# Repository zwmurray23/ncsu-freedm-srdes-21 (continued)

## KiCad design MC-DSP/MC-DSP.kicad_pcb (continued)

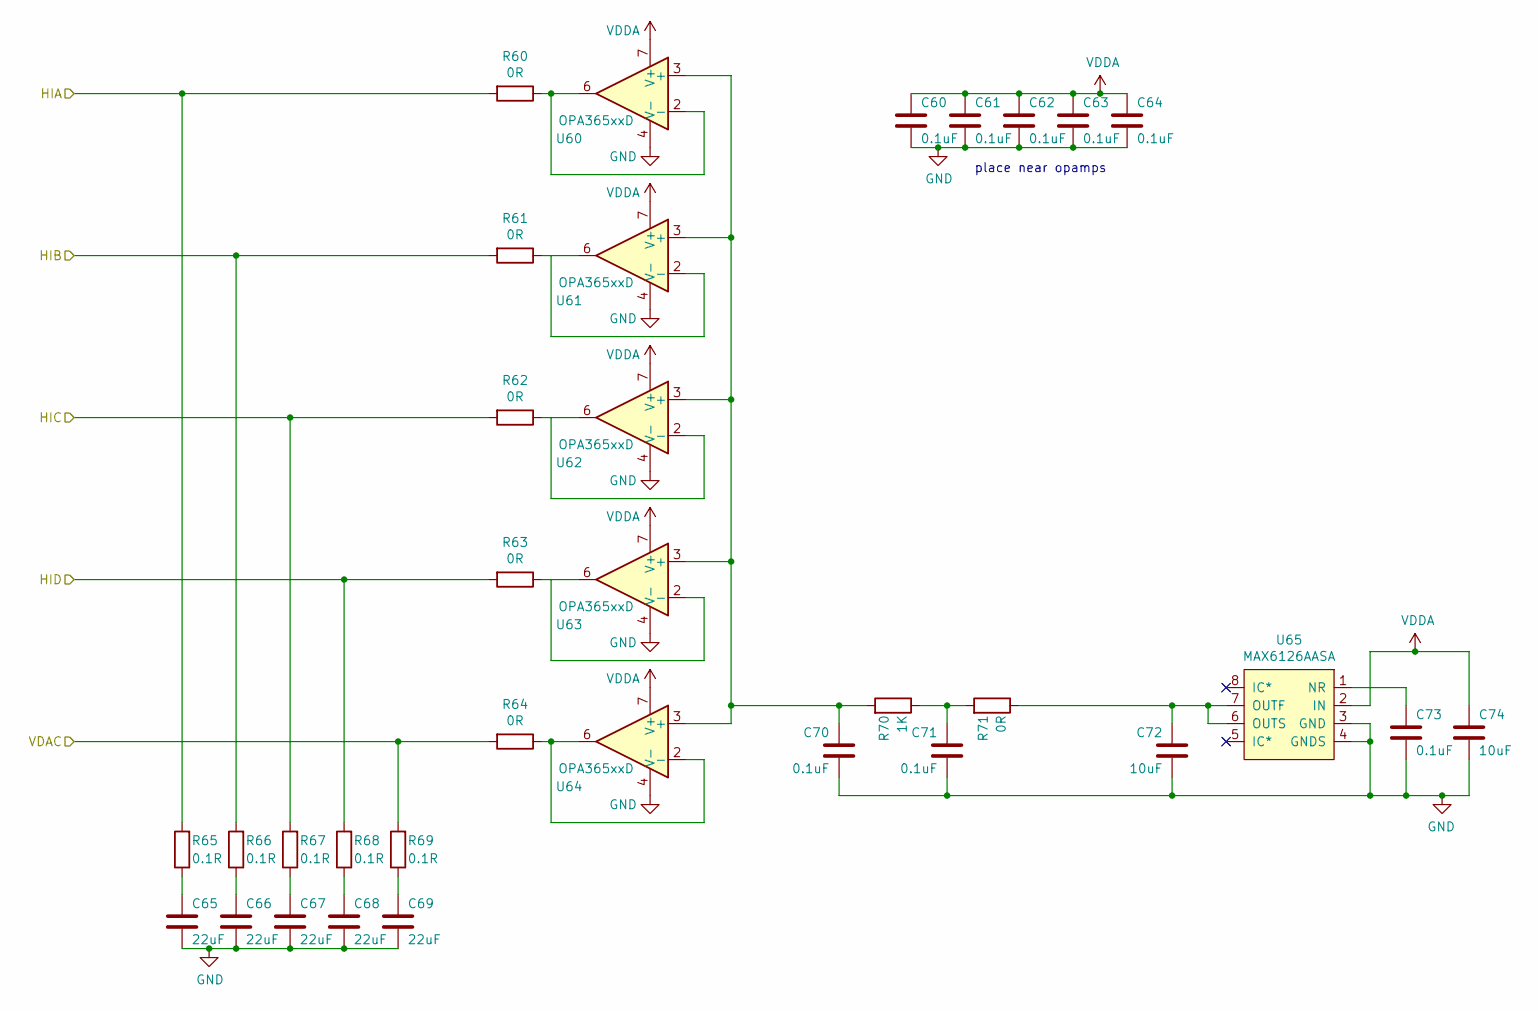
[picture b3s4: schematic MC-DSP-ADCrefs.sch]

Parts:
C60, C61, C62, C63, C64, C70, C71, C73: 0.1uF; C_0603_1608Metric_Pad1.08x0.95mm_HandSolder
C65, C66, C67, C68, C69: 22uF; C_0603_1608Metric_Pad1.08x0.95mm_HandSolder
C72, C74: 10uF; C_0603_1608Metric_Pad1.08x0.95mm_HandSolder
R60, R61, R62, R63, R64, R71: 0R; R_0603_1608Metric_Pad0.98x0.95mm_HandSolder
R65, R66, R67, R68, R69: 0.1R; R_0603_1608Metric_Pad0.98x0.95mm_HandSolder
R70: 1K; R_0603_1608Metric_Pad0.98x0.95mm_HandSolder
U60, U61, U62, U63, U64: OPA365xxD; SOIC-8_3.9x4.9mm_P1.27mm
U65: MAX6126AASA; SOIC-8_3.9x4.9mm_P1.27mm

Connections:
/ADCrefs/HIA: R60.2, R65.2; also elsewhere on the board
/ADCrefs/HIB: R61.2, R66.2; also elsewhere on the board
/ADCrefs/HIC: R62.2, R67.2; also elsewhere on the board
/ADCrefs/HID: R63.2, R68.2; also elsewhere on the board
GND: C60.1, C61.1, C62.1, C63.1, C64.1, C65.1, C66.1, C67.1, C68.1, C69.1, C70.1, C71.1, C72.1, C73.1, C74.1, U60.4 (V-), U61.4 (V-), U62.4 (V-), U63.4 (V-), U64.4 (V-), U65.3 (GND), U65.4 (GNDS); also elsewhere on the board
unnamed: C65.2, R65.1
unnamed: C66.2, R66.1
unnamed: C67.2, R67.1
unnamed: C68.2, R68.1
unnamed: C69.2, R69.1
unnamed: C70.2, R70.2, U60.3 (+), U61.3 (+), U62.3 (+), U63.3 (+), U64.3 (+)
unnamed: C71.2, R70.1, R71.2
unnamed: C72.2, R71.1, U65.6 (OUTS), U65.7 (OUTF)
unnamed: C73.2, U65.1 (NR)
unnamed: R60.1, U60.2 (-), U60.6
unnamed: R61.1, U61.6
unnamed: R62.1, U62.6
unnamed: R63.1, U63.6
unnamed: R64.1, U64.2 (-), U64.6
VDAC: R64.2, R69.2; also elsewhere on the board
VDDA: C60.2, C61.2, C62.2, C63.2, C64.2, C74.2, U60.7 (V+), U61.7 (V+), U62.7 (V+), U63.7 (V+), U64.7 (V+), U65.2 (IN); also elsewhere on the board

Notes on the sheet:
place near opamps

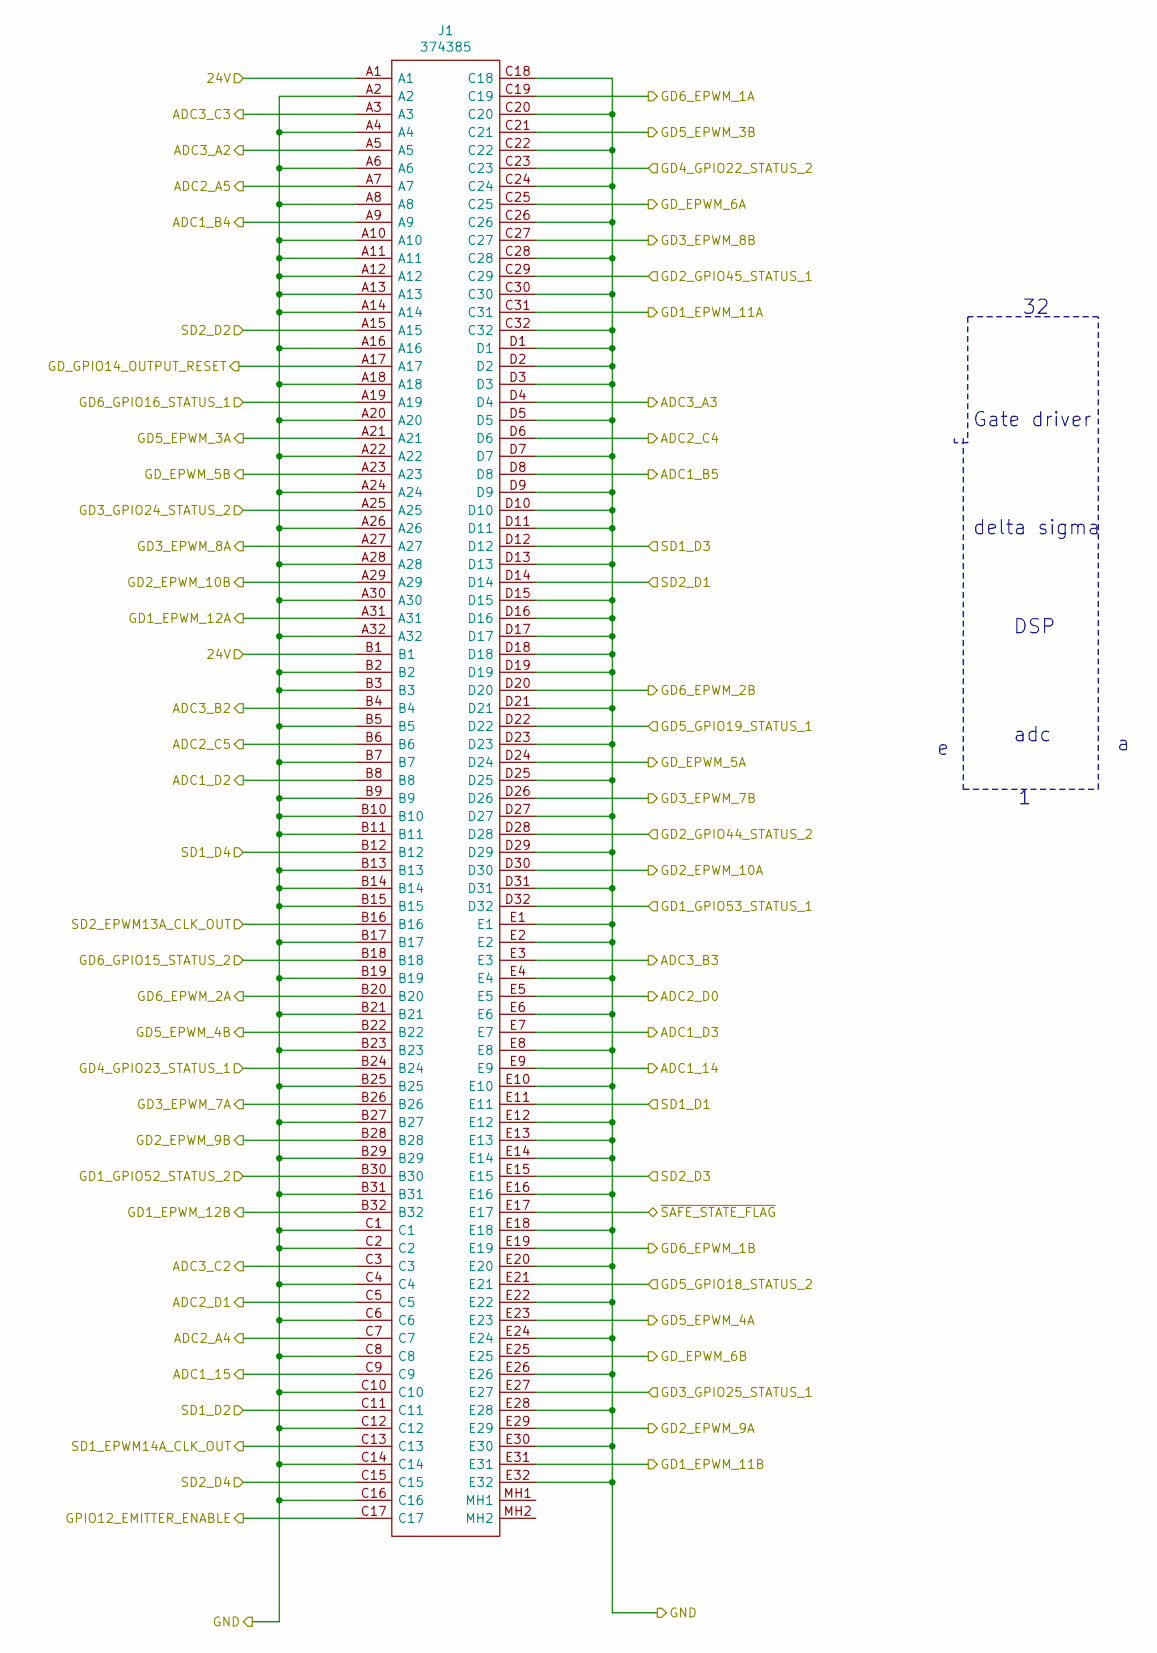
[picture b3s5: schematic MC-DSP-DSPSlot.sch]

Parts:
J1: 374385; Mouser Part Number 305-374385

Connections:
+24V: J1.A1, J1.B1; also elsewhere on the board
/ADC_14: J1.E9; also elsewhere on the board
/ADC_15: J1.C9; also elsewhere on the board
/ADC_A2: J1.A5; also elsewhere on the board
/ADC_A3: J1.D4; also elsewhere on the board
/ADC_A4: J1.C7; also elsewhere on the board
/ADC_A5: J1.A7; also elsewhere on the board
/ADC_B2: J1.B4; also elsewhere on the board
/ADC_B3: J1.E3; also elsewhere on the board
/ADC_B4: J1.A9; also elsewhere on the board
/ADC_B5: J1.D8; also elsewhere on the board
/ADC_C2: J1.C3; also elsewhere on the board
/ADC_C3: J1.A3; also elsewhere on the board
/ADC_C4: J1.D6; also elsewhere on the board
/ADC_C5: J1.B6; also elsewhere on the board
/ADC_D0: J1.E5; also elsewhere on the board
/ADC_D1: J1.C5; also elsewhere on the board
/ADC_D2: J1.B8; also elsewhere on the board
/ADC_D3: J1.E7; also elsewhere on the board
/EPWM1A: J1.C19; also elsewhere on the board
/EPWM1B: J1.E19; also elsewhere on the board
/EPWM2A: J1.B20; also elsewhere on the board
/EPWM2B: J1.D20; also elsewhere on the board
/EPWM3A: J1.A21; also elsewhere on the board
/EPWM3B: J1.C21; also elsewhere on the board
/EPWM4A: J1.E23; also elsewhere on the board
/EPWM4B: J1.B22; also elsewhere on the board
/EPWM5A: J1.D24; also elsewhere on the board
/EPWM5B: J1.A23; also elsewhere on the board
/EPWM6A: J1.C25; also elsewhere on the board
/EPWM6B: J1.E25; also elsewhere on the board
/EPWM7A: J1.B26; also elsewhere on the board
/EPWM7B: J1.D26; also elsewhere on the board
/EPWM8A: J1.A27; also elsewhere on the board
/EPWM8B: J1.C27; also elsewhere on the board
/EPWM9A: J1.E29; also elsewhere on the board
/EPWM9B: J1.B28; also elsewhere on the board
/EPWM10A: J1.D30; also elsewhere on the board
/EPWM10B: J1.A29; also elsewhere on the board
/EPWM11A: J1.C31; also elsewhere on the board
/EPWM11B: J1.E31; also elsewhere on the board
/EPWM12A: J1.A31; also elsewhere on the board
/EPWM12B: J1.B32; also elsewhere on the board
/EPWM13A: J1.B16; also elsewhere on the board
/EPWM14A: J1.C13; also elsewhere on the board
/Emitter_Enable: J1.C17; also elsewhere on the board
/GPIO14: J1.A17; also elsewhere on the board
/GPIO15: J1.B18; also elsewhere on the board
/GPIO16: J1.A19; also elsewhere on the board
/GPIO18: J1.E21; also elsewhere on the board
/GPIO19: J1.D22; also elsewhere on the board
/GPIO22: J1.C23; also elsewhere on the board
/GPIO23: J1.B24; also elsewhere on the board
/GPIO24: J1.A25; also elsewhere on the board
/GPIO25: J1.E27; also elsewhere on the board
/GPIO44: J1.D28; also elsewhere on the board
/GPIO45: J1.C29; also elsewhere on the board
/GPIO52: J1.B30; also elsewhere on the board
/GPIO53: J1.D32; also elsewhere on the board
/SD1_D1: J1.E11; also elsewhere on the board
/SD1_D2: J1.C11; also elsewhere on the board
/SD1_D3: J1.D12; also elsewhere on the board
/SD1_D4: J1.B12; also elsewhere on the board
/SD2_D1: J1.D14; also elsewhere on the board
/SD2_D2: J1.A15; also elsewhere on the board
/SD2_D3: J1.E15; also elsewhere on the board
/SD2_D4: J1.C15; also elsewhere on the board
/Safe_State: J1.E17; also elsewhere on the board
GND: J1.A2, J1.A4, J1.A6, J1.A8, J1.A10, J1.A11, J1.A12, J1.A13, J1.A14, J1.A16, J1.A18, J1.A20, J1.A22, J1.A24, J1.A26, J1.A28, J1.A30, J1.A32, J1.B2, J1.B3, J1.B5, J1.B7, J1.B9, J1.B10, J1.B11, J1.B13, J1.B14, J1.B15, J1.B17, J1.B19, J1.B21, J1.B23, J1.B25, J1.B27, J1.B29, J1.B31, J1.C1, J1.C2, J1.C4, J1.C6, J1.C8, J1.C10, J1.C12, J1.C14, J1.C16, J1.C18, J1.C20, J1.C22, J1.C24, J1.C26, J1.C28, J1.C30, J1.C32, J1.D1, J1.D2, J1.D3, J1.D5, J1.D7, J1.D9, J1.D10, J1.D11, J1.D13, J1.D15, J1.D16, J1.D17, J1.D18, J1.D19, J1.D21, J1.D23, J1.D25, J1.D27, J1.D29, J1.D31, J1.E1, J1.E2, J1.E4, J1.E6, J1.E8, J1.E10, J1.E12, J1.E13, J1.E14, J1.E16, J1.E18, J1.E20, J1.E22, J1.E24, J1.E26, J1.E28, J1.E30, J1.E32; also elsewhere on the board

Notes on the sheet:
adc
DSP
delta sigma
Gate driver

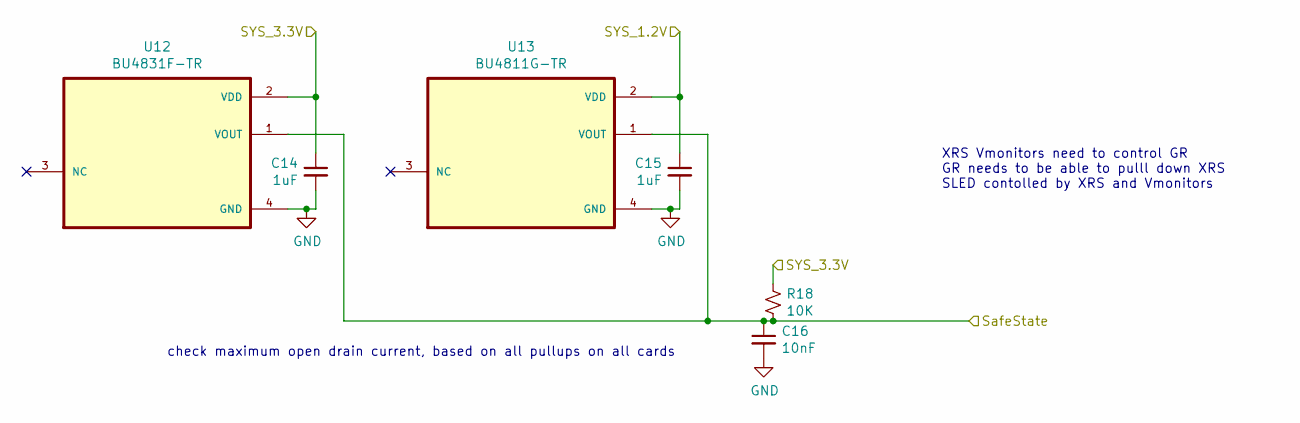
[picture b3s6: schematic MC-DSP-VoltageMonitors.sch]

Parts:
C14, C15: 1uF; C_0603_1608Metric_Pad1.08x0.95mm_HandSolder
C16: 10nF; C_0603_1608Metric_Pad1.08x0.95mm_HandSolder
R18: 10K; R_0603_1608Metric_Pad0.98x0.95mm_HandSolder
U12: BU4831F-TR; SOP4
U13: BU4811G-TR; TSOP-5_1.65x3.05mm_P0.95mm

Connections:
+3V3: C14.1, R18.1, U12.2 (VDD); also elsewhere on the board
/Safe_State: C16.1, R18.2, U12.1 (VOUT), U13.1 (VOUT); also elsewhere on the board
/Voltage Regulators/SYS_1.2V: C15.1, U13.2 (VDD); also elsewhere on the board
GND: C14.2, C15.2, C16.2, U12.4 (GND), U13.4 (GND); also elsewhere on the board

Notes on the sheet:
XRS Vmonitors need to control GR GR needs to be able to pulll down XRS SLED contolled by XRS and Vmonitors
check maximum open drain current, based on all pullups on all cards

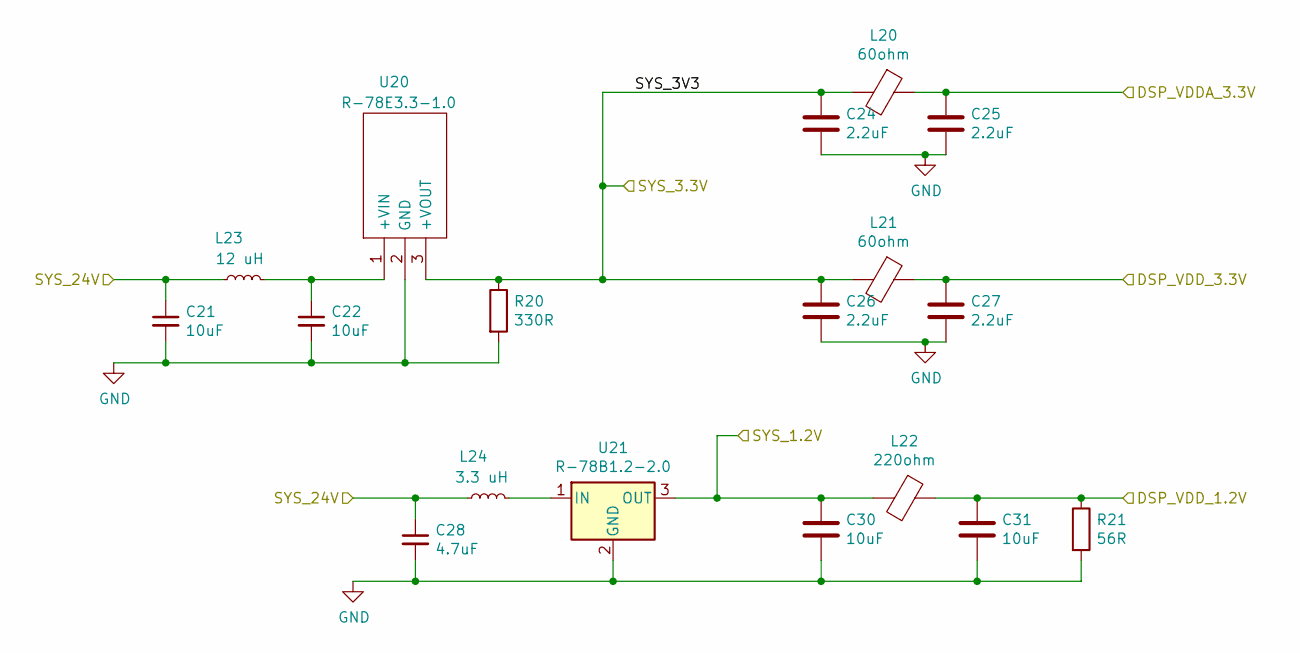
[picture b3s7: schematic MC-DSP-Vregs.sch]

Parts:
C21, C22: 10uF; C_1210_3225Metric
C24, C25, C26, C27: 2.2uF; C_0603_1608Metric_Pad1.08x0.95mm_HandSolder
C28: 4.7uF; C_1210_3225Metric
C30, C31: 10uF; C_0603_1608Metric_Pad1.08x0.95mm_HandSolder
L20, L21: 60ohm; L_0805_2012Metric_Pad1.05x1.20mm_HandSolder
L22: 220ohm; L_0805_2012Metric_Pad1.05x1.20mm_HandSolder
L23: 12 uH; L_Radial_D8.7mm_P5.00mm_Fastron_07HCP
L24: 3.3 uH; L_Radial_D8.7mm_P5.00mm_Fastron_07HCP
R20: 330R; R_0603_1608Metric_Pad0.98x0.95mm_HandSolder
R21: 56R; R_0603_1608Metric_Pad0.98x0.95mm_HandSolder
U20: R-78E3.3-1.0; Converter_DCDC_RECOM_R-78B-2.0_THT
U21: R-78B1.2-2.0; Converter_DCDC_RECOM_R-78B-2.0_THT

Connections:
+1V2: C31.1, L22.1, R21.1; also elsewhere on the board
+3V3: C24.2, C26.2, L20.2, L21.2, R20.1, U20.3 (+VOUT); also elsewhere on the board
+24V: C21.1, C28.1, L23.1, L24.1; also elsewhere on the board
/Voltage Regulators/SYS_1.2V: C30.2, L22.2, U21.3 (OUT); also elsewhere on the board
GND: C21.2, C22.2, C24.1, C25.2, C26.1, C27.2, C28.2, C30.1, C31.2, R20.2, R21.2, U20.2 (GND), U21.2 (GND); also elsewhere on the board
unnamed: C22.1, L23.2, U20.1 (+VIN)
unnamed: L24.2, U21.1 (IN)
VDD: C27.1, L21.1; also elsewhere on the board
VDDA: C25.1, L20.1; also elsewhere on the board

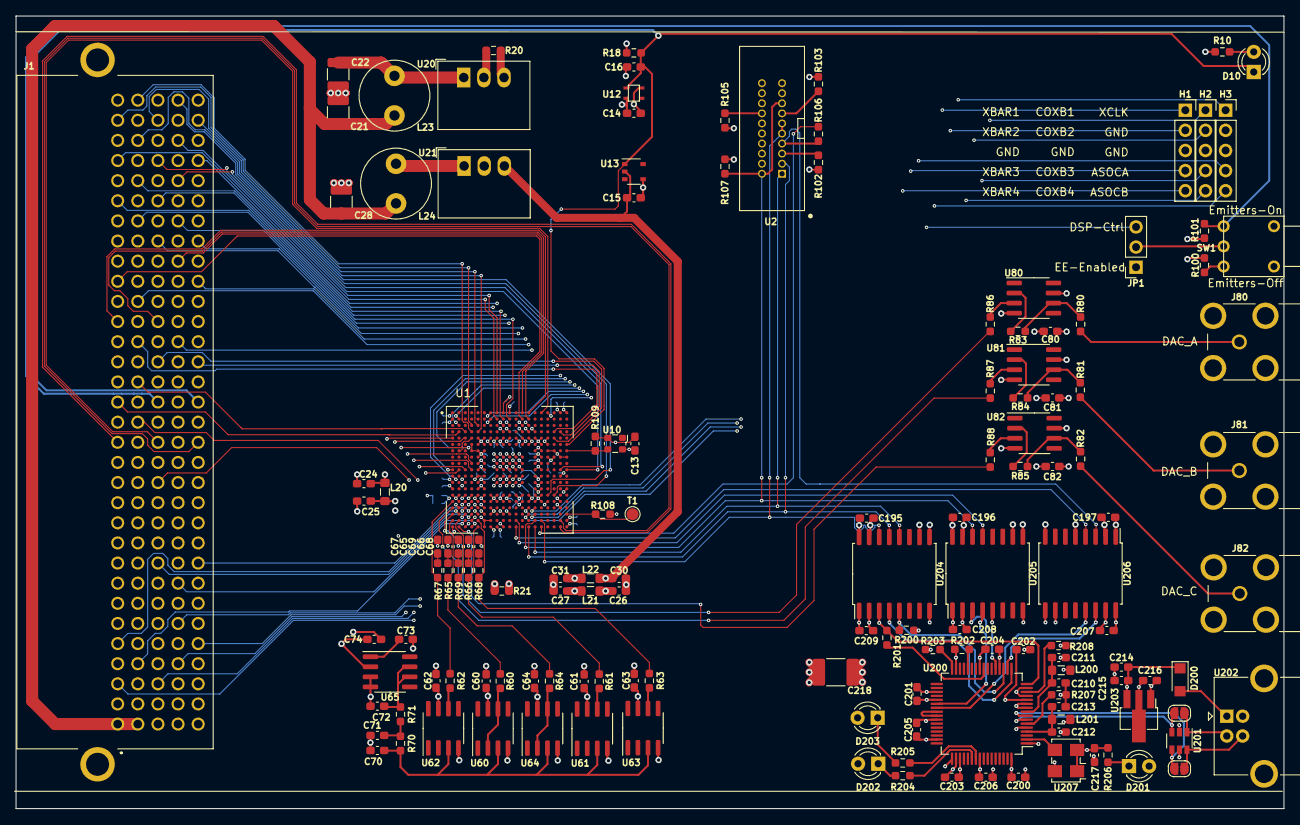
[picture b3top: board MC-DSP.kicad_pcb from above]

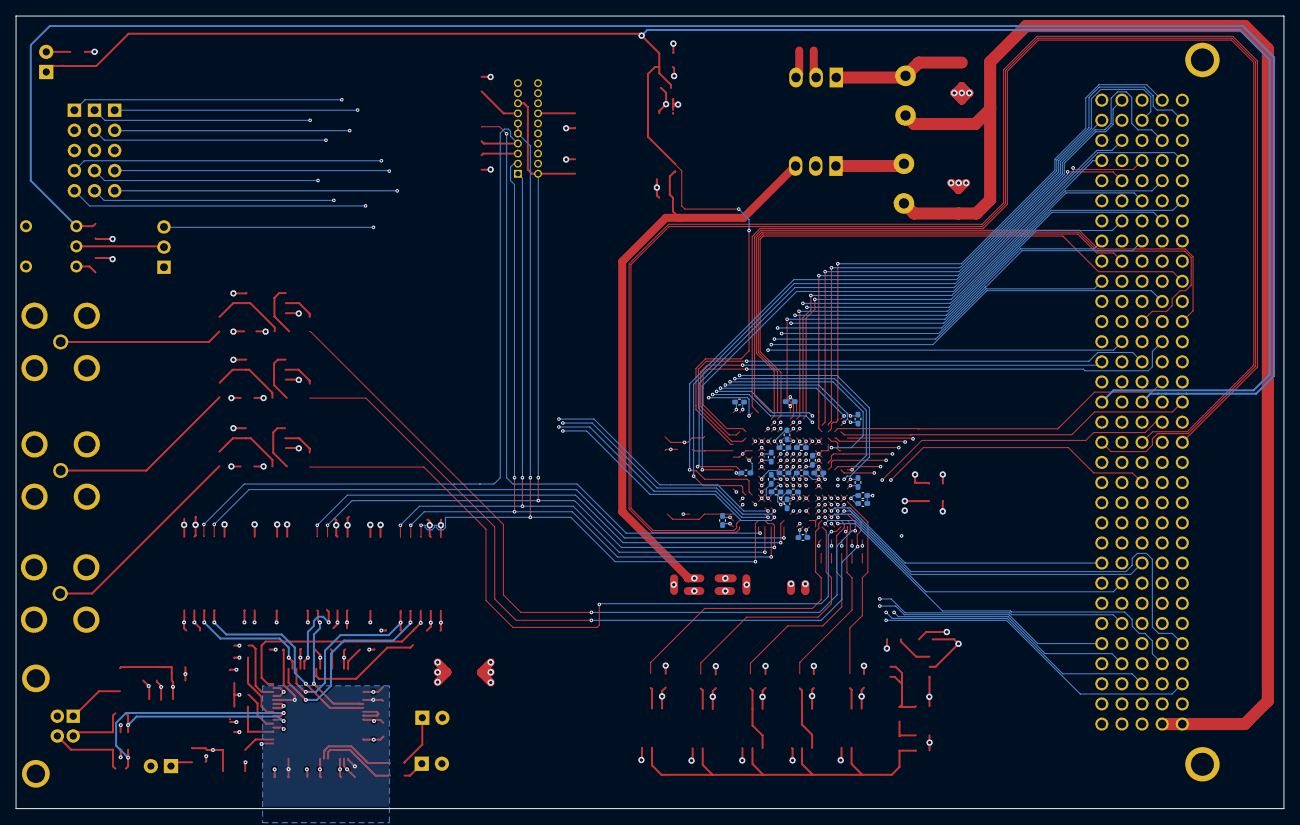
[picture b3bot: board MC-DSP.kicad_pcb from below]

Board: 6 copper layers, 160.0 x 100.0 mm, 165 parts (21 on the bottom side), 168 nets.

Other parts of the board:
C218: 10pF 3000V; C_1812_4532Metric_Pad1.57x3.40mm_HandSolder

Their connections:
EMU_GND: C218.1; also elsewhere on the board
GND: C218.2; also elsewhere on the board

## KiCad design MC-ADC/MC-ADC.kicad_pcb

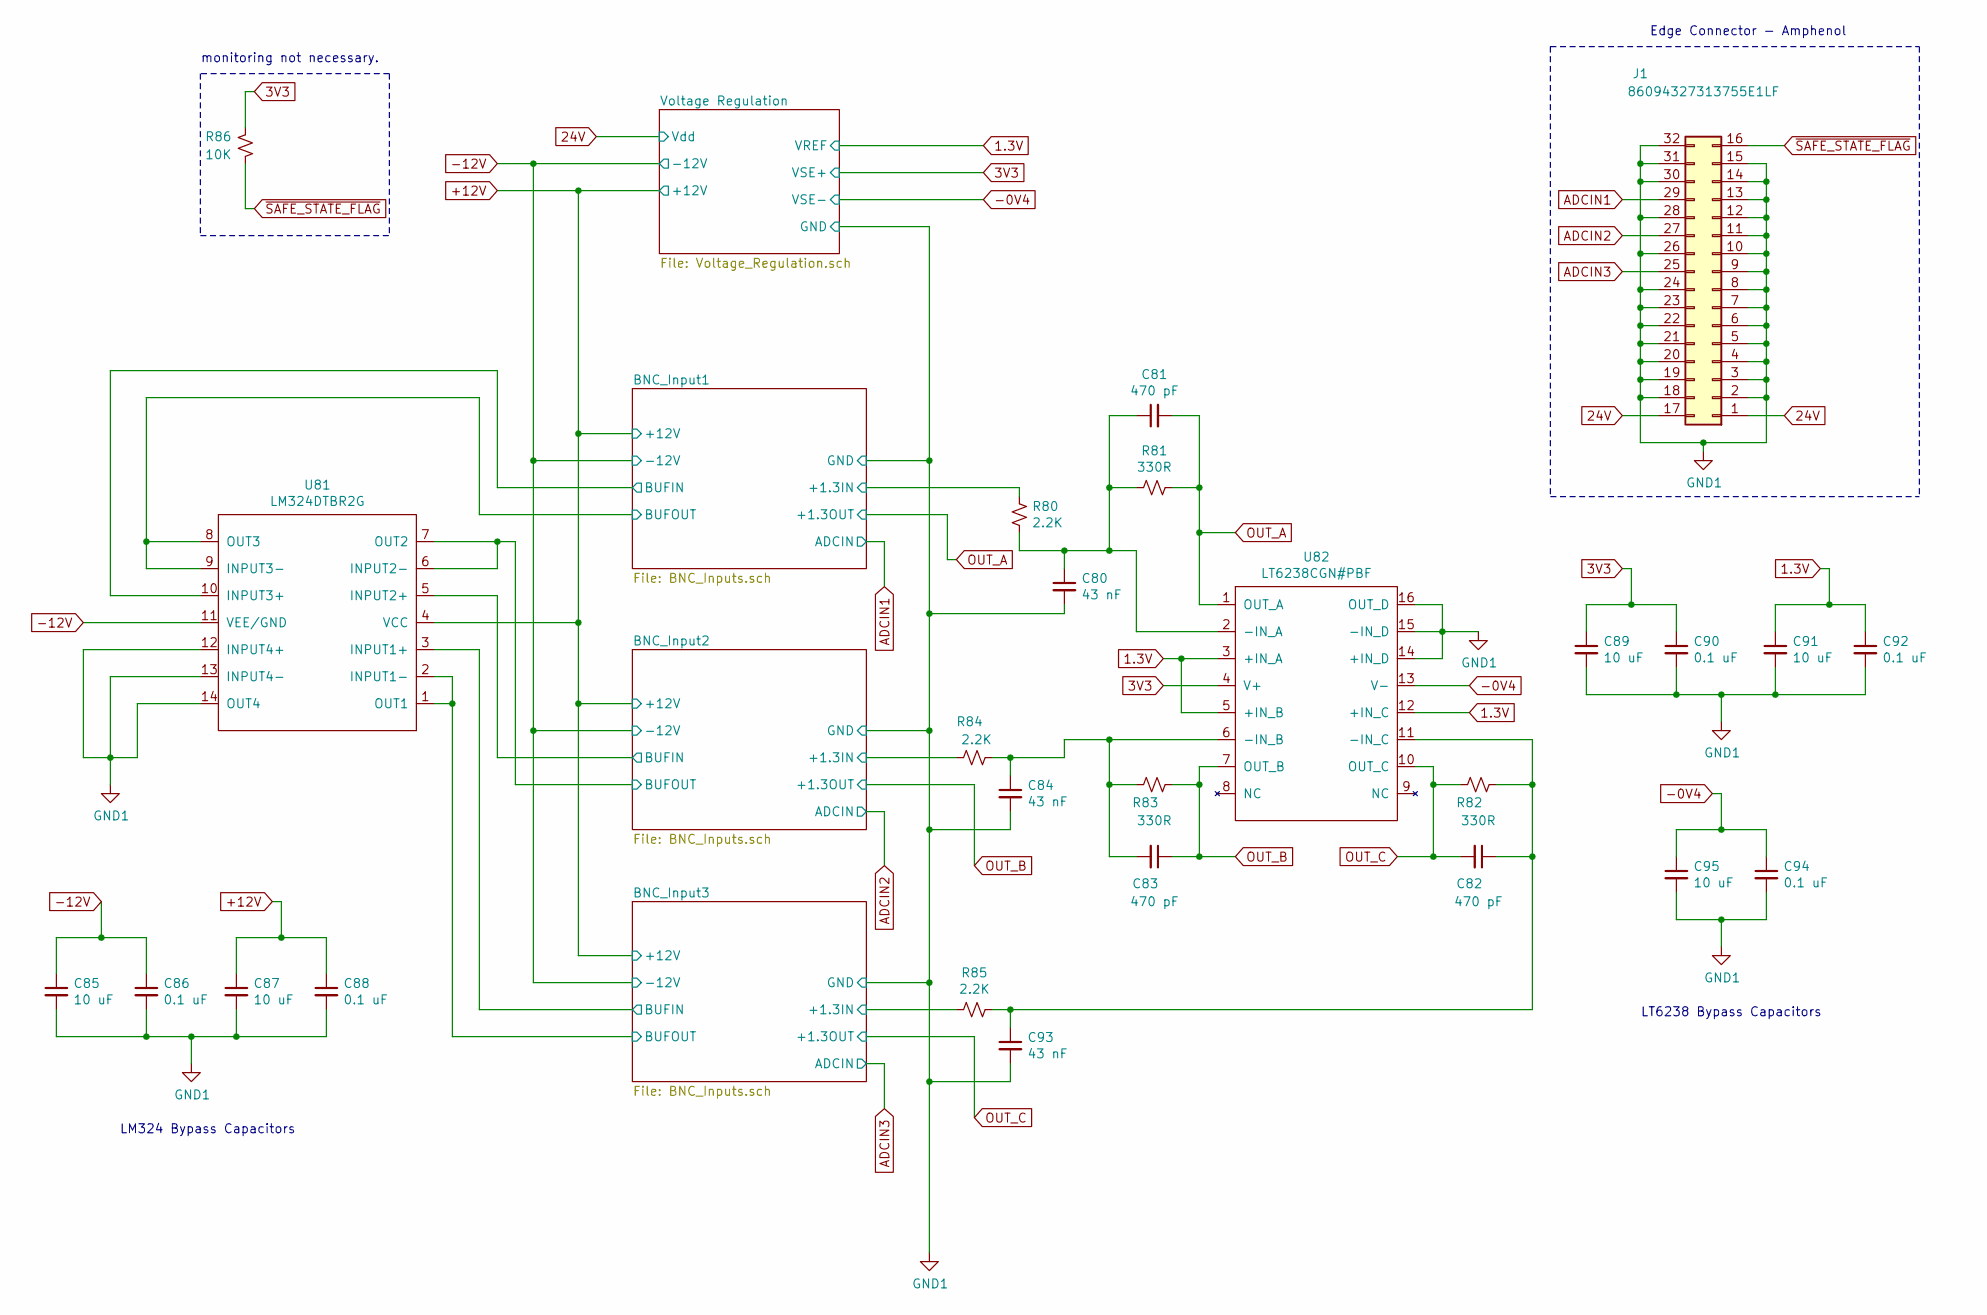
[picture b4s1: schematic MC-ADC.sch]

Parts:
C80, C84, C93: 43 nF; C_0805_2012Metric
C81, C82, C83: 470 pF; C_1206_3216Metric
C85, C87, C89, C91, C95: 10 uF; C_1210_3225Metric
C86, C88, C90, C92, C94: 0.1 uF; C_1210_3225Metric
J1: 86094327313755E1LF
R80, R84, R85: 2.2K; R_1206_3216Metric
R81, R82, R83: 330R; R_0603_1608Metric
R86: 10K; R_1206_3216Metric
U81: LM324DTBR2G
U82: LT6238CGN#PBF; SSOP-16_3.9x4.9mm_P0.635mm

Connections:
1.3V: C91.1, C92.1, U82.3 (+IN_A), U82.5 (+IN_B), U82.12 (+IN_C); also elsewhere on the board
3V3: C89.1, C90.1, R86.2, U82.4 (V+); also elsewhere on the board
24V: J1.1, J1.17; also elsewhere on the board
+12V: C87.1, C88.1, U81.4 (VCC); also elsewhere on the board
-0V4: C94.1, C95.1, U82.13 (V-); also elsewhere on the board
-12V: C85.1, C86.1, U81.11 (VEE/GND); also elsewhere on the board
/BNC_Input1/+1.3IN: R80.1; also elsewhere on the board
/BNC_Input1/BUFIN: U81.10 (INPUT3+); also elsewhere on the board
/BNC_Input1/BUFOUT: U81.8 (OUT3), U81.9 (INPUT3-); also elsewhere on the board
/BNC_Input2/+1.3IN: R84.1; also elsewhere on the board
/BNC_Input2/BUFIN: U81.5 (INPUT2+); also elsewhere on the board
/BNC_Input2/BUFOUT: U81.6 (INPUT2-), U81.7 (OUT2); also elsewhere on the board
/BNC_Input3/+1.3IN: R85.1; also elsewhere on the board
/BNC_Input3/BUFIN: U81.3 (INPUT1+); also elsewhere on the board
/BNC_Input3/BUFOUT: U81.1 (OUT1), U81.2 (INPUT1-); also elsewhere on the board
ADCIN1: J1.29; also elsewhere on the board
ADCIN2: J1.27; also elsewhere on the board
ADCIN3: J1.25; also elsewhere on the board
GND1: C80.2, C84.2, C85.2, C86.2, C87.2, C88.2, C89.2, C90.2, C91.2, C92.2, C93.2, C94.2, C95.2, J1.2, J1.3, J1.4, J1.5, J1.6, J1.7, J1.8, J1.9, J1.10, J1.11, J1.12, J1.13, J1.14, J1.15, J1.18, J1.19, J1.20, J1.21, J1.22, J1.23, J1.24, J1.26, J1.28, J1.30, J1.31, J1.32, U81.12 (INPUT4+), U81.13 (INPUT4-), U81.14 (OUT4), U82.14 (+IN_D), U82.15 (-IN_D), U82.16 (OUT_D); also elsewhere on the board
unnamed: C80.1, C81.1, R80.2, R81.1, U82.2 (-IN_A)
unnamed: C82.1, C93.1, R82.1, R85.2, U82.11 (-IN_C)
unnamed: C83.2, C84.1, R83.2, R84.2, U82.6 (-IN_B)
OUT_A: C81.2, R81.2, U82.1 (OUT_A); also elsewhere on the board
OUT_B: C83.1, R83.1, U82.7 (OUT_B); also elsewhere on the board
OUT_C: C82.2, R82.2, U82.10 (OUT_C); also elsewhere on the board
~SAFE_STATE_FLAG: J1.16, R86.1

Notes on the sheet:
Edge Connector - Amphenol
monitoring not necessary.
LM324 Bypass Capacitors
LT6238 Bypass Capacitors

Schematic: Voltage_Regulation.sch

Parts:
C10: 4.7 uF; C_1210_3225Metric
C11: 2.2 uF; C_1210_3225Metric
C12, C13, C18: unpopulated; C_1210_3225Metric
C14, C15, C17: 0.1 uF; C_1210_3225Metric
C16: 10 uF; C_1210_3225Metric
L10: 3.9 uH; L_1812_4532Metric_Pad1.30x3.40mm_HandSolder
L11: 10uH
R10: 1.87K; R_0603_1608Metric
R11: 1.43K; R_0603_1608Metric
R12: 30.9K; R_1206_3216Metric
R13: 1.07K; R_1206_3216Metric
U10: MAX6216
U11: R-78E3.3-0.5
U12: NMK2412SC

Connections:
1.3V: R10.2, R11.1; also elsewhere on the board
3V3: C18.1, U11.3 (+VOUT); also elsewhere on the board
24V: C10.1, C11.1, C15.1, L10.1, L11.1, U10.2; also elsewhere on the board
+12V: C13.1, U12.6; also elsewhere on the board
-12V: C12.2, R12.1, U12.4; also elsewhere on the board
GND1: C10.2, C11.2, C12.1, C13.2, C14.2, C15.2, C16.2, C17.2, C18.2, R11.2, R13.2, U10.3, U10.4, U11.2 (GND), U12.2, U12.5; also elsewhere on the board
unnamed: C14.1, U10.1
unnamed: C16.1, C17.1, R10.1, U10.6, U10.7
unnamed: L10.2, U11.1 (+VIN)
unnamed: L11.2, U12.1
unnamed: R12.2, R13.1

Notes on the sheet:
24V -> +/-12V Circuit
24V -> 3.3V Circuit
1.3V
Approx. -0.4V
Approx. 3.3V
+/- 11.64 to 12.6V
-0.421V to -0.389V

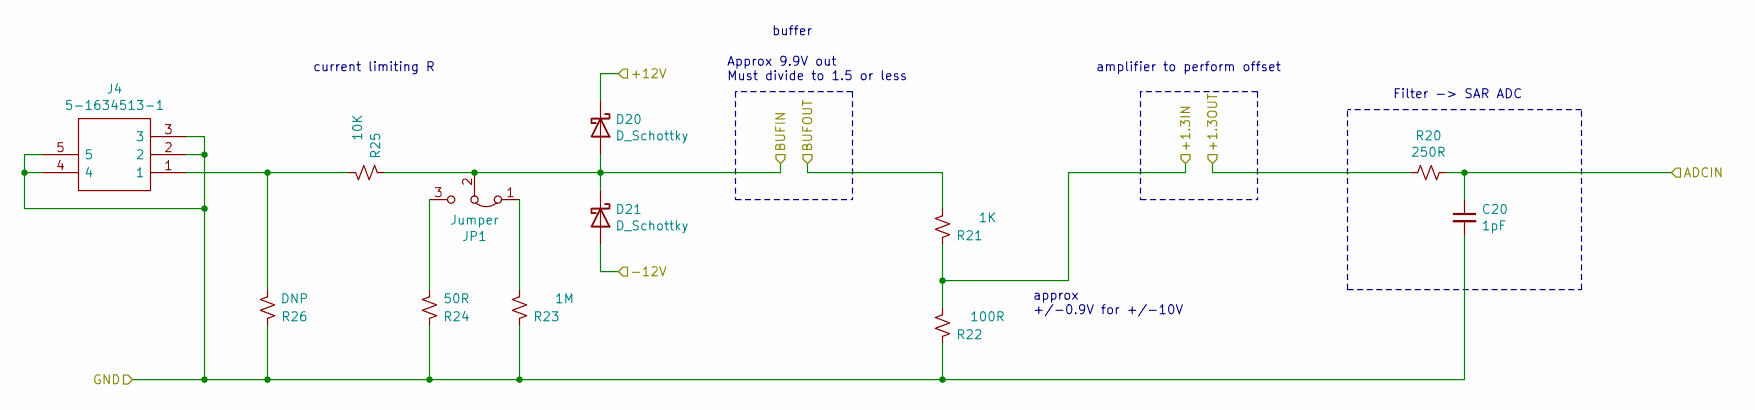
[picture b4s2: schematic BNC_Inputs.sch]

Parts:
C20: 1pF; C_0603_1608Metric
D20, D21: D_Schottky; SOT-23
J4: 5-1634513-1; 516345131; Manufacturer_Part_Number 5-1634513-1; Mouser Part Number 571-5-1634513-1
JP1: Jumper; PinHeader_1x03_P2.54mm_Vertical
R20: 250R; R_0603_1608Metric
R21: 1K; R_0805_2012Metric
R22: 100R; R_0603_1608Metric
R23: 1M; R_1206_3216Metric
R24: 50R; R_0603_1608Metric
R25: 10K; R_1206_3216Metric
R26: DNP; R_1206_3216Metric

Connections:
+12V: D20.1 (K); also elsewhere on the board
-12V: D21.2 (A); also elsewhere on the board
/BNC_Input1/+1.3IN: R21.2, R22.1; also elsewhere on the board
/BNC_Input1/BUFIN: D20.2 (A), D21.1 (K), JP1.2 (C), R25.2; also elsewhere on the board
/BNC_Input1/BUFOUT: R21.1; also elsewhere on the board
ADCIN1: C20.1, R20.1; also elsewhere on the board
GND1: C20.2, J4.2, J4.3, J4.4, J4.5, R22.2, R23.2, R24.2, R26.2; also elsewhere on the board
unnamed: J4.1, R25.1, R26.1
unnamed: JP1.1 (A), R23.1
unnamed: JP1.3 (B), R24.1
OUT_A: R20.2; also elsewhere on the board

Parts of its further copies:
C30, C40: 1pF; C_0603_1608Metric
D30, D31, D41, D42: D_Schottky; SOT-23
J2, J3: 5-1634513-1; 516345131; Manufacturer_Part_Number 5-1634513-1; Mouser Part Number 571-5-1634513-1
JP2, JP3: Jumper; PinHeader_1x03_P2.54mm_Vertical
R30, R40: 250R; R_0603_1608Metric
R31, R41: 100R; R_0603_1608Metric
R32, R42: 1K; R_0805_2012Metric
R33, R43: 1M; R_1206_3216Metric
R34, R44: 50R; R_0603_1608Metric
R35, R45: 10K; R_1206_3216Metric
R36, R46: DNP; R_1206_3216Metric

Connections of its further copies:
+12V: D30.1 (K), D41.1 (K); also elsewhere on the board
-12V: D31.2 (A), D42.2 (A); also elsewhere on the board
/BNC_Input2/+1.3IN: R31.1, R32.2; also elsewhere on the board
/BNC_Input2/BUFIN: D30.2 (A), D31.1 (K), JP2.2 (C), R35.2; also elsewhere on the board
/BNC_Input2/BUFOUT: R32.1; also elsewhere on the board
/BNC_Input3/+1.3IN: R41.1, R42.2; also elsewhere on the board
/BNC_Input3/BUFIN: D41.2 (A), D42.1 (K), JP3.2 (C), R45.2; also elsewhere on the board
/BNC_Input3/BUFOUT: R42.1; also elsewhere on the board
ADCIN2: C30.1, R30.1; also elsewhere on the board
ADCIN3: C40.1, R40.1; also elsewhere on the board
GND1: C30.2, C40.2, J2.2, J2.3, J2.4, J2.5, J3.2, J3.3, J3.4, J3.5, R31.2, R33.2, R34.2, R36.2, R41.2, R43.2, R44.2, R46.2; also elsewhere on the board
unnamed: J2.1, R35.1, R36.1
unnamed: J3.1, R45.1, R46.1
unnamed: JP2.1 (A), R33.1
unnamed: JP2.3 (B), R34.1
unnamed: JP3.1 (A), R43.1
unnamed: JP3.3 (B), R44.1
OUT_B: R30.2; also elsewhere on the board
OUT_C: R40.2; also elsewhere on the board

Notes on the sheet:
Filter -> SAR ADC
buffer
amplifier to perform offset
current limiting R
Approx 9.9V out Must divide to 1.5 or less
approx +/-0.9V for +/-10V

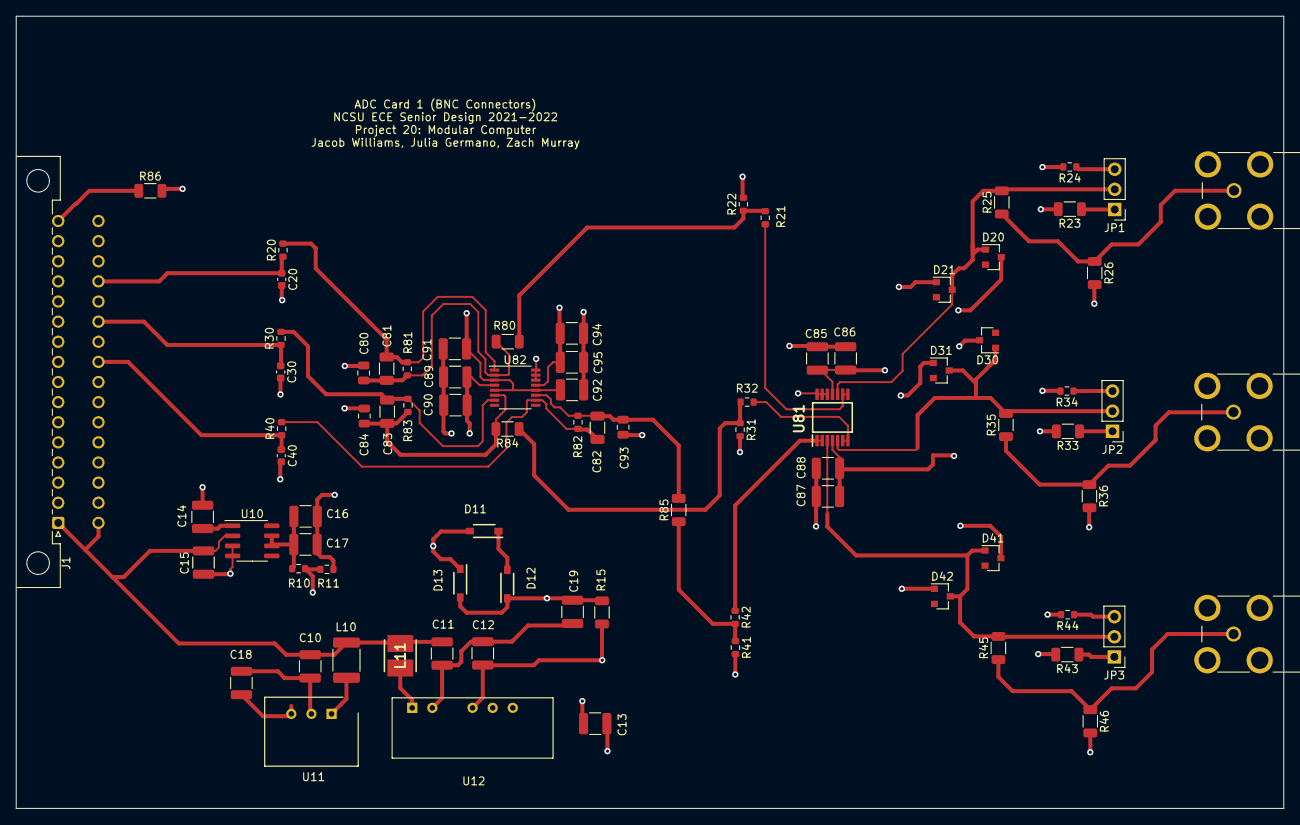
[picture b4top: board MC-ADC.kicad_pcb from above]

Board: 4 copper layers, 160.0 x 100.0 mm, 83 parts (0 on the bottom side), 40 nets.

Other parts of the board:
C19: 10uF; C_1210_3225Metric
D11, D12, D13: MBR0520L; SOD3716X135N
R15: 1.5K; R_1206_3216Metric

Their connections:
-0V4: C19.2, D12.1, D13.2, R15.1; also elsewhere on the board
-12V: R15.2; also elsewhere on the board
GND1: C19.1, D11.2, D13.1; also elsewhere on the board
unnamed: D11.1, D12.2

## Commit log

2021-09-29 test proper ssh access
2021-10-20 LED Prelim Schematics Upload
2021-10-20 Emitter CKT in progress
2021-10-20 Update team member listing
2021-10-21 Add IC Models
2021-10-21 New model library
2021-10-21 Add detector schematics, update hierarchy
2021-10-21 create dsp folder
2021-10-21 update new ic's
2021-10-21 Added Voltage Reg. CKTs
2021-10-21 moved FO Board to using hierarchical sheets
2021-10-22 Add files via upload
    added rest of emitters/detectors and power led
2021-10-25 Updated naming, Pi filters
2021-10-25 Updated LED Ckts, Added new IC model
2021-10-25 5V tolerant logic to Detector and designators
2021-10-26 a few more FO tweaks 10-26
2021-10-27 added footprints and reference
2021-10-27 LED symbol
2021-10-28 floating pins fix, signal name updates
2021-10-28 C31-34 larger packaging and part assignment
2021-10-28 remove part # on Cap...getting ahead of myself
2021-10-28 Fixed floating pins, added notes
2021-10-29 unpopulated cap after voltage regulators
    and changed reference designator numbering scheme
    and moved the or gate that sends 3.3 V to comparator in detector ckt
2021-10-30 many changes
    -one ground
    -RESET_FO added
    -pull down resistors on resets, status and pwm
    -Detector 1 ckt OR gate after comparator
2021-10-30 pull down resistor footprint
2021-10-30 Fixed file hierarchy
2021-10-30 Detector2 update, RESET integration
2021-10-30 add connector, reset implementation
2021-10-30 reset implementation, connector
2021-11-01 update footprints, resistors
2021-11-01 removed outdated FO Board files
2021-11-01 add connector files
2021-11-01 Connector Footprint
2021-11-01 Linked footprint for connector
2021-11-03 changed status1 to output of detector
    reassigned footprint of 550 LED
2021-11-03 PCB Layout begins
    - read in the netlist
    - drew the edge of the card
    - moved the footprints around
    - 4 layer board, parts on front only
2021-11-04 routing prep/organization
    moving detectors/emitters around to find where to put status LED
2021-11-05 Update LED, Transc. Footprint, layout
2021-11-06 Removed AND-OR gates
2021-11-08 DSP schem, FO schem, and FO layout changes
2021-11-08 Routed FO schematic
    All FO circuits routed except LED and Detector circuits.
2021-11-08 Changed V-monitor circuit, V-reg circuit, finished detectors
2021-11-08 24V line and LED ckrt fix
2021-11-09 First gerber file version for FO card
2021-11-09 added bottom solder mask to gerbers
2022-01-19 updated top level of schematic with "to test" and "to do" notes
2022-01-21 Add ADC card project
2022-01-21 Create Backplane
2022-01-24 Minor ADC work
2022-01-24 added reverse polarity protection circuit and fuse
2022-01-25 pmos swap, fuse cartridge, power conn
2022-01-26 ADC Work
2022-02-01 added signals for FO slots
2022-02-02 Significant ADC Progress
2022-02-14 Add files via upload
    updating net names and wires
2022-02-16 ADC Updates!
2022-02-18 Signal naming cleanup/ dsp pin pairing
2022-02-21 ADC refs, FTDI changes, and more
2022-02-21 Prep for DSP connector
2022-02-21 fixed some dsp pin routing
2022-02-28 updating SAFE_STATE_FLAG and EMITTER_ENABLE
2022-03-01 schematic changes--> layout rev
2022-03-02 Pre final revision Layout
2022-03-04 simplify vias, mechanical hole change
2022-03-07 All parts labeled, just need to pick passives basically.
2022-03-07 DSP interface pin out
2022-03-08 beginning layout
2022-03-09 schematic reorg and layout begins
2022-03-09 ADC Work + Start Layout
2022-03-09 ADC Work + Layout
2022-03-09 DSP - added footprints and links to most parts
2022-03-09 Sim upload
2022-03-09 ADC work for Alpha
2022-03-09 Removed clock buffer, misc leds, ethernet
2022-03-09 placement done- tracks started
2022-03-11 ADC LAYOUT
2022-03-11 layout done: cleaning up and checking MH
2022-03-11 Prelim ADC layout complete
2022-03-12 Layout done: ready for revisions
    - double check measurements and connector placement
    -passes DRC schematic and layout
2022-03-12 Layout ready for review
    - double check measurements and connector placement
2022-03-12 Layout Revision
    -removed MH1 from emitter/detector symbol
    -pin out changes to assist with routing on the backplane
2022-03-14 some DRC edits and pinout changes
    still need to:
    - add gnd test points
    - fix pad too close to pad errors
    - spread the reference vias on the traces that change layers farther apart
    -allow more layout around U2 and U3 in the layout due to 24V
2022-03-14 spread tracks across available space
    could still add some test points
2022-03-14 DRC error fixes, added gnd testpoints
2022-03-14 DRC error fixes and gnd test points added
2022-03-14 added testpoints
2022-03-16 removed some MHs and attempted to fix library
2022-03-16 slot label correction
2022-03-18 moved global lib to project lib
2022-03-19 added backplane connector, changed right angle headers, added FP for bigger reg caps, all ICs arranged, routed isolated section.
2022-03-21 connected DSP signals to BP connector symbol, routed most non-signal traces on PCB
2022-03-22 ADC Gerbers Generated
2022-03-30 Total overhaul of power planes. Routed whole Analog section, middle of digital section.
2022-03-31 DSP breakout to backplane done, just need to route final 11 signals.
2022-04-01 fixed V7 gnd issue
2022-04-01 Fixed all DSP symbol and footprint Library paths to be implicit
2022-04-01 Fixed ADC ref low pass filter positions (moved them closer to the DSP) and fixed board outline
2022-04-01 Routed Last 11 tracks, fixed cu.4 gnd pour
2022-04-01 Added labels on the silkscreen
2022-04-01 generated gerbers
2022-04-16 - updated PMOSFET&Zener footprint
    reverse polarity protection circuit
2022-04-26 Voltage detector footprint correction
2022-04-26 increased 24V trace width.
